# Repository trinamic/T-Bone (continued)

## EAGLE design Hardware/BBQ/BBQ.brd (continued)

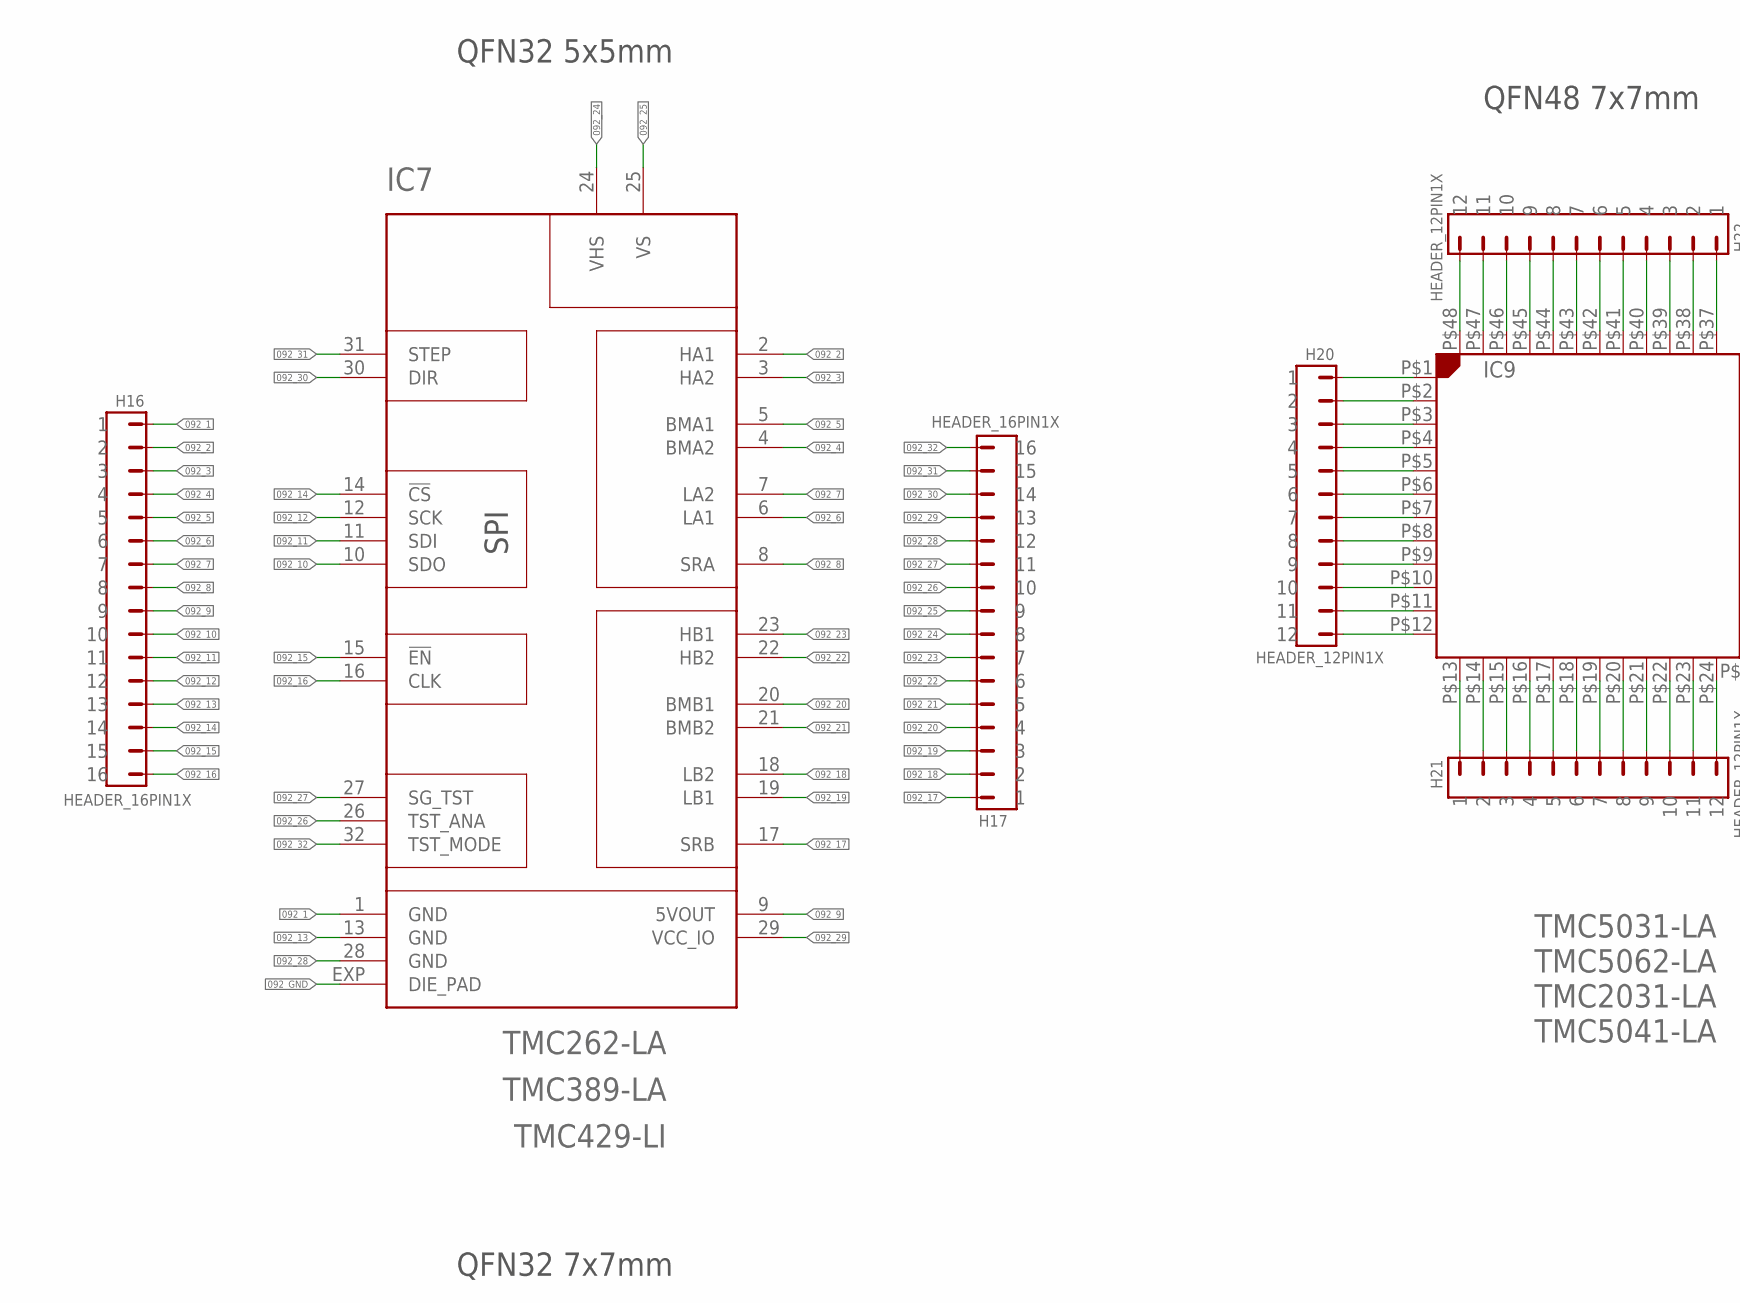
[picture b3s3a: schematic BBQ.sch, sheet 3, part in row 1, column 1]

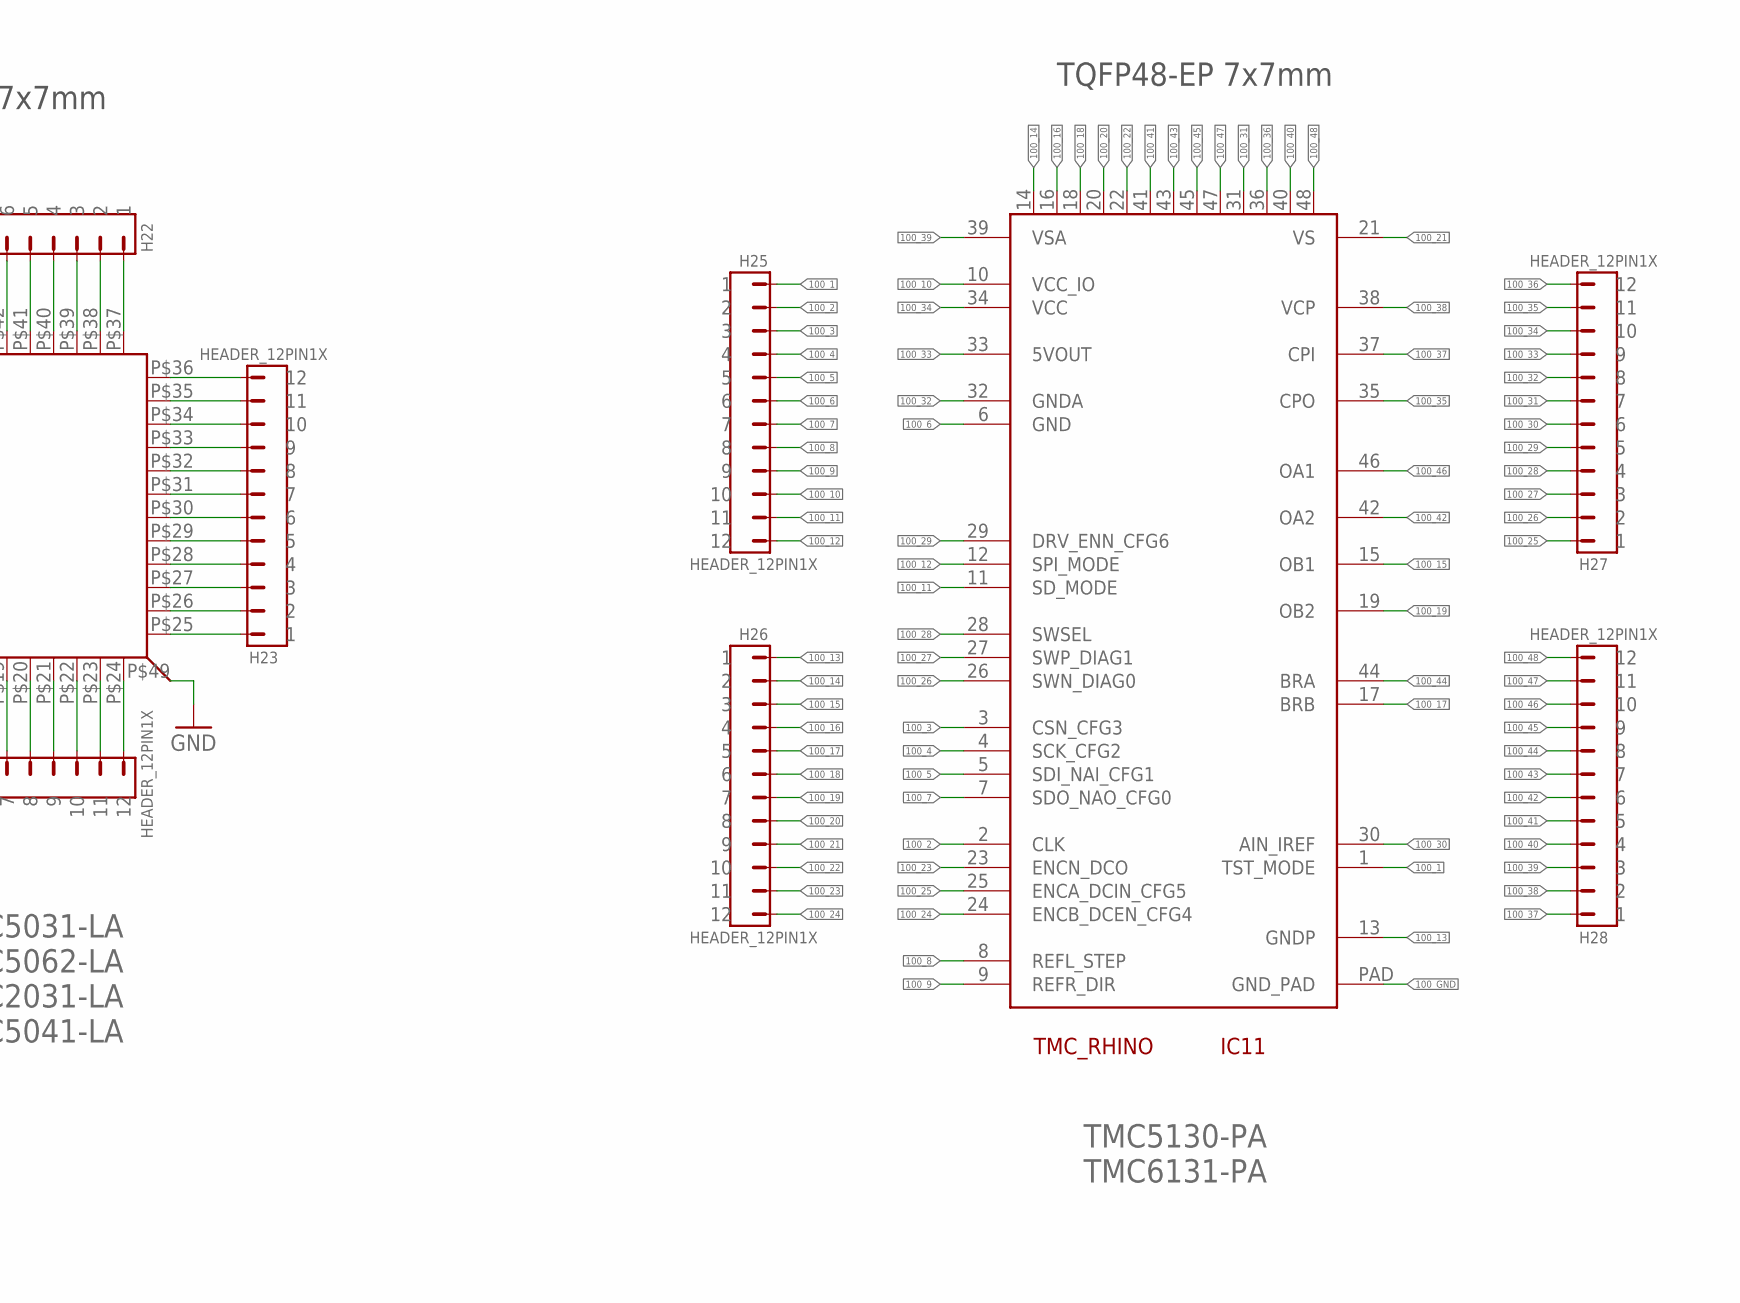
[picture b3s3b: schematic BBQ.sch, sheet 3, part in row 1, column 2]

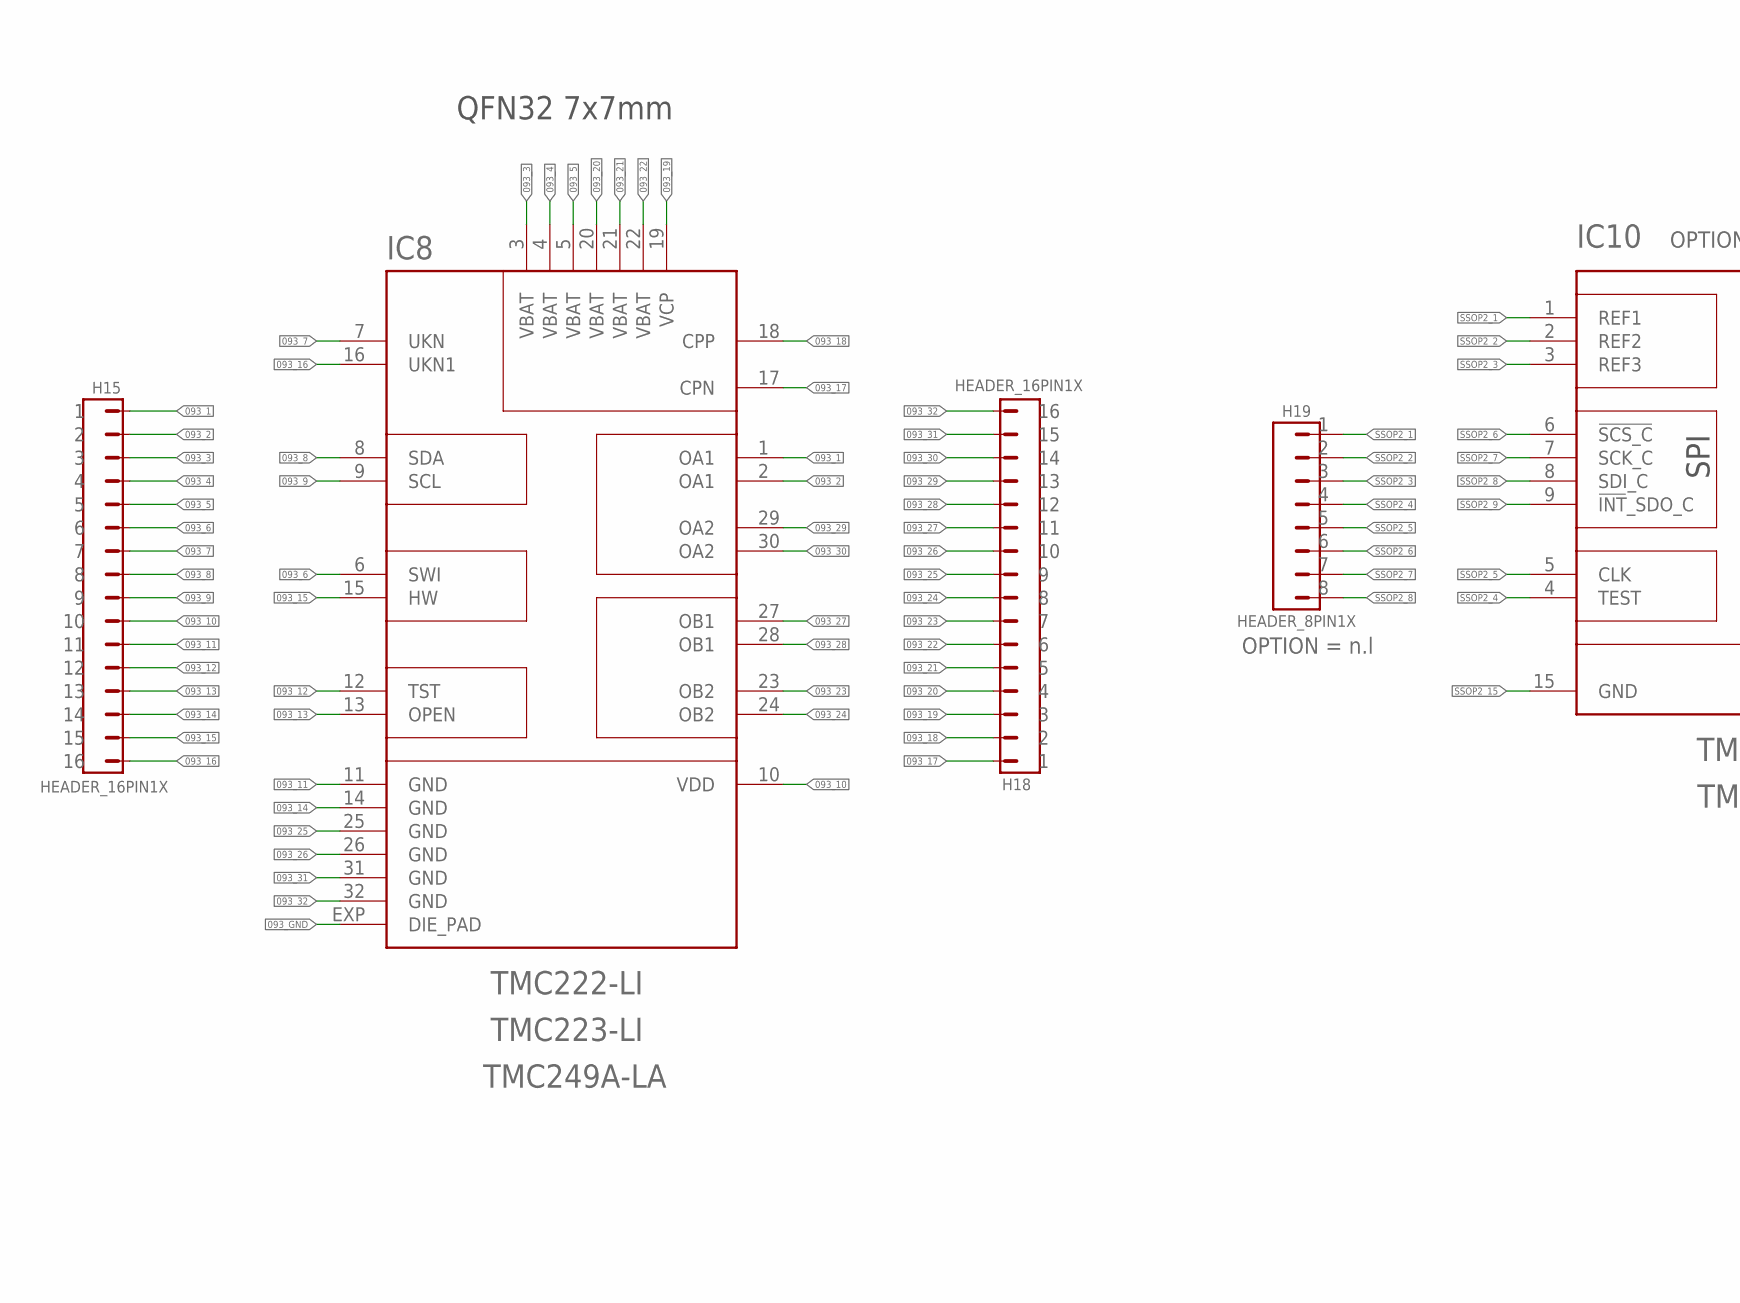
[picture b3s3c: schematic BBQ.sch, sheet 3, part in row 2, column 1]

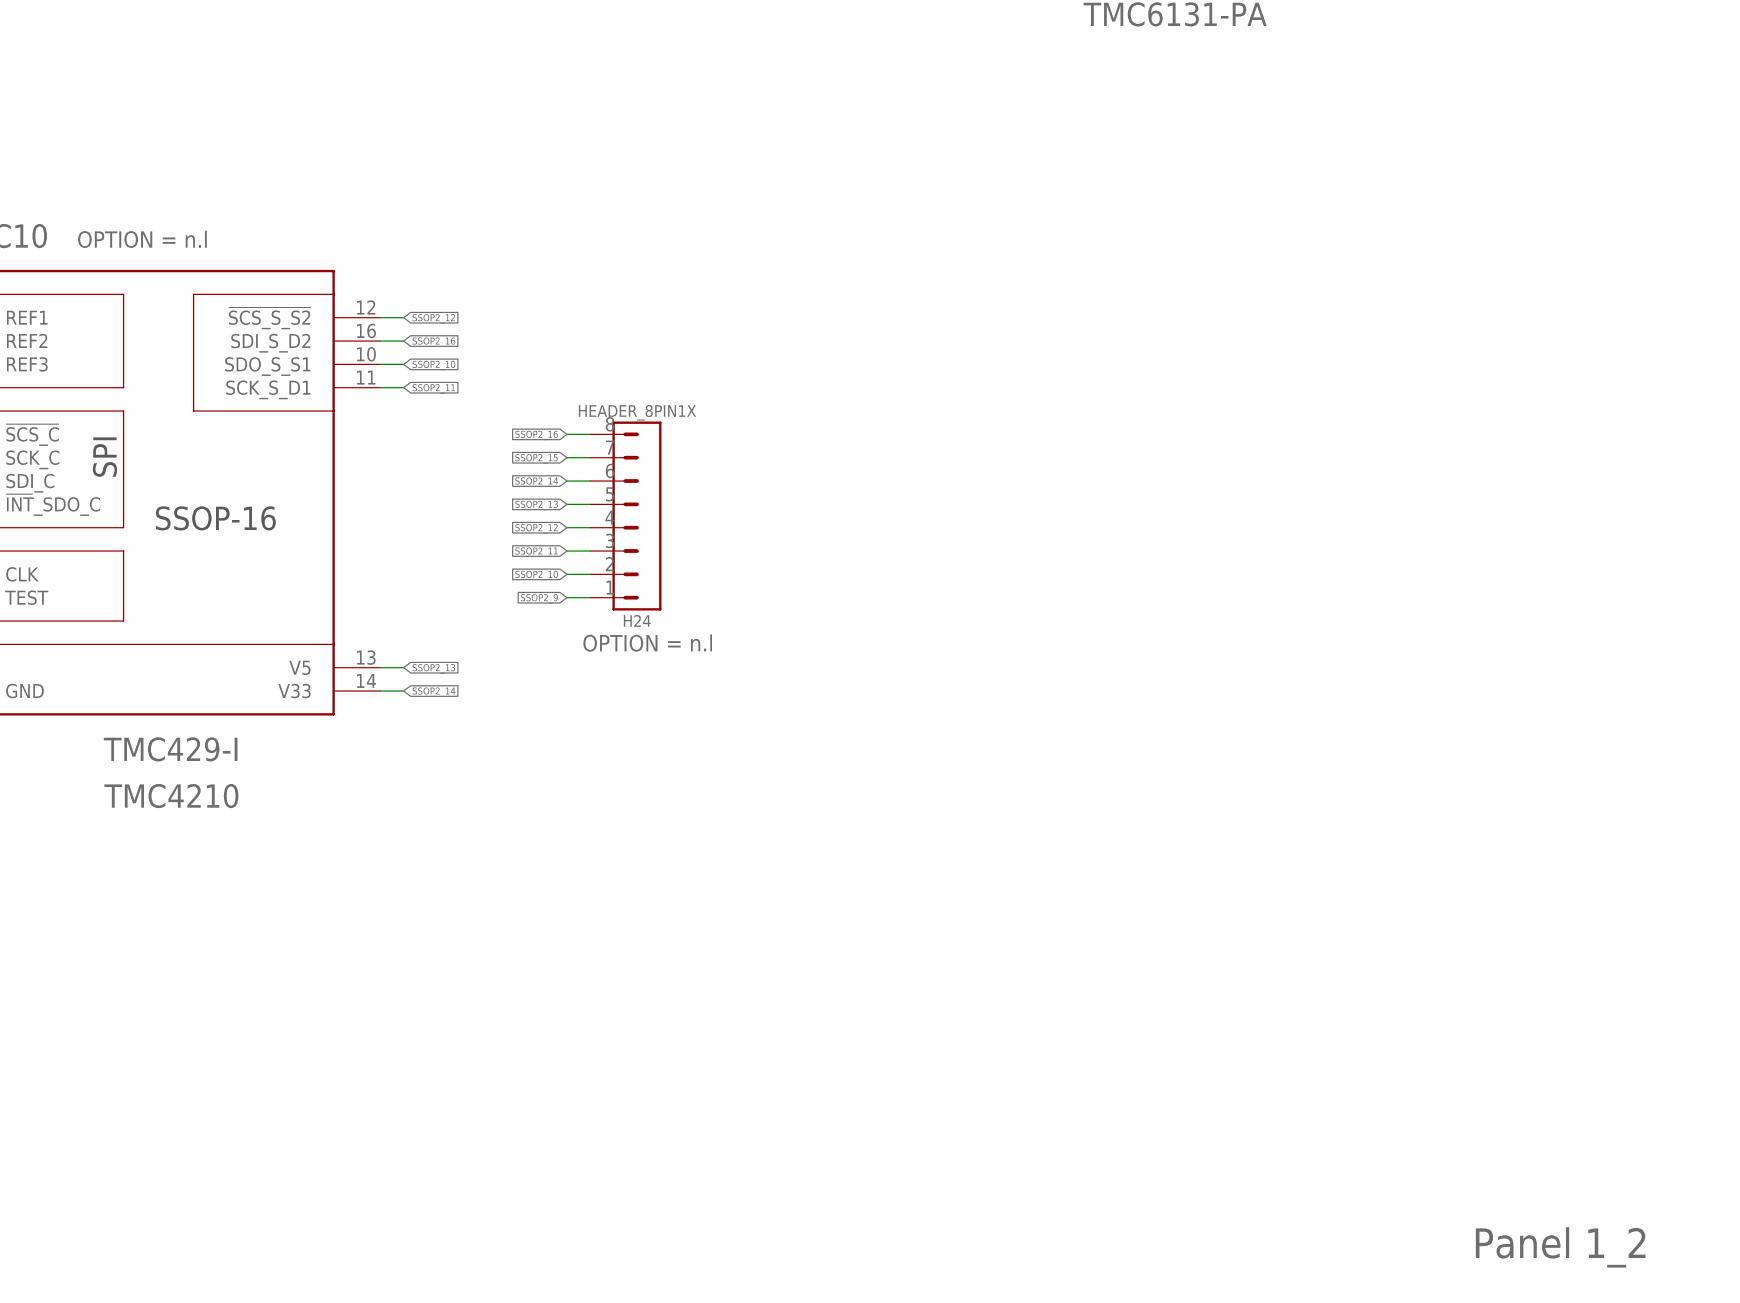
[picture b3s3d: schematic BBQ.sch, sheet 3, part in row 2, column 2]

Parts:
H15, H16, H17, H18: HEADER_16PIN1X; 16PIN_2.54_TH
H19, H24: HEADER_8PIN1X; 8PIN_2.54_TH
H20, H21, H22, H23, H25, H26, H27, H28: HEADER_12PIN1X; 12PIN_2.54_TH
IC7: TMC262-LA; QFN32_5X5
IC8: TMC222-LI; QFN32_7X7
IC9: TMC5031-LA; QFN-48_7X7
IC10: TMC429-I; SSOP16
IC11: TMC_RHINO; TQFP48-EP

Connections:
092_1: H16.1, IC7.1 (GND)
092_2: H16.2, IC7.2 (HA1)
092_3: H16.3, IC7.3 (HA2)
092_4: H16.4, IC7.4 (BMA2)
092_5: H16.5, IC7.5 (BMA1)
092_6: H16.6, IC7.6 (LA1)
092_7: H16.7, IC7.7 (LA2)
092_8: H16.8, IC7.8 (SRA)
092_9: H16.9, IC7.9 (5VOUT)
092_10: H16.10, IC7.10 (SDO)
092_11: H16.11, IC7.11 (SDI)
092_12: H16.12, IC7.12 (SCK)
092_13: H16.13, IC7.13 (GND)
092_14: H16.14, IC7.14 (!CS)
092_15: H16.15, IC7.15 (!EN)
092_16: H16.16, IC7.16 (CLK)
092_17: H17.1, IC7.17 (SRB)
092_18: H17.2, IC7.18 (LB2)
092_19: H17.3, IC7.19 (LB1)
092_20: H17.4, IC7.20 (BMB1)
092_21: H17.5, IC7.21 (BMB2)
092_22: H17.6, IC7.22 (HB2)
092_23: H17.7, IC7.23 (HB1)
092_24: H17.8, IC7.24 (VHS)
092_25: H17.9, IC7.25 (VS)
092_26: H17.10, IC7.26 (TST_ANA)
092_27: H17.11, IC7.27 (SG_TST)
092_28: H17.12, IC7.28 (GND)
092_29: H17.13, IC7.29 (VCC_IO)
092_30: H17.14, IC7.30 (DIR)
092_31: H17.15, IC7.31 (STEP)
092_32: H17.16, IC7.32 (TST_MODE)
092_GND: IC7.EXP (DIE_PAD)
093_1: H15.1, IC8.1 (OA1)
093_2: H15.2, IC8.2 (OA1)
093_3: H15.3, IC8.3 (VBAT)
093_4: H15.4, IC8.4 (VBAT)
093_5: H15.5, IC8.5 (VBAT)
093_6: H15.6, IC8.6 (SWI)
093_7: H15.7, IC8.7 (UKN)
093_8: H15.8, IC8.8 (SDA)
093_9: H15.9, IC8.9 (SCL)
093_10: H15.10, IC8.10 (VDD)
093_11: H15.11, IC8.11 (GND)
093_12: H15.12, IC8.12 (TST)
093_13: H15.13, IC8.13 (OPEN)
093_14: H15.14, IC8.14 (GND)
093_15: H15.15, IC8.15 (HW)
093_16: H15.16, IC8.16 (UKN1)
093_17: H18.1, IC8.17 (CPN)
093_18: H18.2, IC8.18 (CPP)
093_19: H18.3, IC8.19 (VCP)
093_20: H18.4, IC8.20 (VBAT)
093_21: H18.5, IC8.21 (VBAT)
093_22: H18.6, IC8.22 (VBAT)
093_23: H18.7, IC8.23 (OB2)
093_24: H18.8, IC8.24 (OB2)
093_25: H18.9, IC8.25 (GND)
093_26: H18.10, IC8.26 (GND)
093_27: H18.11, IC8.27 (OB1)
093_28: H18.12, IC8.28 (OB1)
093_29: H18.13, IC8.29 (OA2)
093_30: H18.14, IC8.30 (OA2)
093_31: H18.15, IC8.31 (GND)
093_32: H18.16, IC8.32 (GND)
093_GND: IC8.EXP (DIE_PAD)
096_GND: IC9.P$49 (EXP)
100_1: H25.1, IC11.1 (TST_MODE)
100_2: H25.2, IC11.2 (CLK)
100_3: H25.3, IC11.3 (CSN_CFG3)
100_4: H25.4, IC11.4 (SCK_CFG2)
100_5: H25.5, IC11.5 (SDI_NAI_CFG1)
100_6: H25.6, IC11.6 (GND)
100_7: H25.7, IC11.7 (SDO_NAO_CFG0)
100_8: H25.8, IC11.8 (REFL_STEP)
100_9: H25.9, IC11.9 (REFR_DIR)
100_10: H25.10, IC11.10 (VCC_IO)
100_11: H25.11, IC11.11 (SD_MODE)
100_12: H25.12, IC11.12 (SPI_MODE)
100_13: H26.1, IC11.13 (GNDP)
100_14: H26.2, IC11.14
100_15: H26.3, IC11.15 (OB1)
100_16: H26.4, IC11.16
100_17: H26.5, IC11.17 (BRB)
100_18: H26.6, IC11.18
100_19: H26.7, IC11.19 (OB2)
100_20: H26.8, IC11.20
100_21: H26.9, IC11.21 (VS)
100_22: H26.10, IC11.22
100_23: H26.11, IC11.23 (ENCN_DCO)
100_24: H26.12, IC11.24 (ENCB_DCEN_CFG4)
100_25: H27.1, IC11.25 (ENCA_DCIN_CFG5)
100_26: H27.2, IC11.26 (SWN_DIAG0)
100_27: H27.3, IC11.27 (SWP_DIAG1)
100_28: H27.4, IC11.28 (SWSEL)
100_29: H27.5, IC11.29 (DRV_ENN_CFG6)
100_30: H27.6, IC11.30 (AIN_IREF)
100_31: H27.7, IC11.31
100_32: H27.8, IC11.32 (GNDA)
100_33: H27.9, IC11.33 (5VOUT)
100_34: H27.10, IC11.34 (VCC)
100_35: H27.11, IC11.35 (CPO)
100_36: H27.12, IC11.36
100_37: H28.1, IC11.37 (CPI)
100_38: H28.2, IC11.38 (VCP)
100_39: H28.3, IC11.39 (VSA)
100_40: H28.4, IC11.40
100_41: H28.5, IC11.41
100_42: H28.6, IC11.42 (OA2)
100_43: H28.7, IC11.43
100_44: H28.8, IC11.44 (BRA)
100_45: H28.9, IC11.45
100_46: H28.10, IC11.46 (OA1)
100_47: H28.11, IC11.47
100_48: H28.12, IC11.48
100_GND: IC11.PAD (GND_PAD)
unnamed: H20.1, IC9.P$1
unnamed: H20.2, IC9.P$2
unnamed: H20.3, IC9.P$3
unnamed: H20.4, IC9.P$4
unnamed: H20.5, IC9.P$5
unnamed: H20.6, IC9.P$6
unnamed: H20.7, IC9.P$7
unnamed: H20.8, IC9.P$8
unnamed: H20.9, IC9.P$9
unnamed: H20.10, IC9.P$10
unnamed: H20.11, IC9.P$11
unnamed: H20.12, IC9.P$12
unnamed: H21.1, IC9.P$13
unnamed: H21.2, IC9.P$14
unnamed: H21.3, IC9.P$15
unnamed: H21.4, IC9.P$16
unnamed: H21.5, IC9.P$17
unnamed: H21.6, IC9.P$18
unnamed: H21.7, IC9.P$19
unnamed: H21.8, IC9.P$20
unnamed: H21.9, IC9.P$21
unnamed: H21.10, IC9.P$22
unnamed: H21.11, IC9.P$23
unnamed: H21.12, IC9.P$24
unnamed: H23.1, IC9.P$25
unnamed: H23.2, IC9.P$26
unnamed: H23.3, IC9.P$27
unnamed: H23.4, IC9.P$28
unnamed: H23.5, IC9.P$29
unnamed: H23.6, IC9.P$30
unnamed: H23.7, IC9.P$31
unnamed: H23.8, IC9.P$32
unnamed: H23.9, IC9.P$33
unnamed: H23.10, IC9.P$34
unnamed: H23.11, IC9.P$35
unnamed: H23.12, IC9.P$36
unnamed: H22.1, IC9.P$37
unnamed: H22.2, IC9.P$38
unnamed: H22.3, IC9.P$39
unnamed: H22.4, IC9.P$40
unnamed: H22.5, IC9.P$41
unnamed: H22.6, IC9.P$42
unnamed: H22.7, IC9.P$43
unnamed: H22.8, IC9.P$44
unnamed: H22.9, IC9.P$45
unnamed: H22.10, IC9.P$46
unnamed: H22.11, IC9.P$47
unnamed: H22.12, IC9.P$48
SSOP2_1: H19.1, IC10.1 (REF1)
SSOP2_2: H19.2, IC10.2 (REF2)
SSOP2_3: H19.3, IC10.3 (REF3)
SSOP2_4: H19.4, IC10.4 (TEST)
SSOP2_5: H19.5, IC10.5 (CLK)
SSOP2_6: H19.6, IC10.6 (!SCS_C)
SSOP2_7: H19.7, IC10.7 (SCK_C)
SSOP2_8: H19.8, IC10.8 (SDI_C)
SSOP2_9: H24.1, IC10.9 (!INT!_SDO_C)
SSOP2_10: H24.2, IC10.10 (SDO_S_S1)
SSOP2_11: H24.3, IC10.11 (SCK_S_D1)
SSOP2_12: H24.4, IC10.12 (!SCS_S_S2)
SSOP2_13: H24.5, IC10.13 (V5)
SSOP2_14: H24.6, IC10.14 (V33)
SSOP2_15: H24.7, IC10.15 (GND)
SSOP2_16: H24.8, IC10.16 (SDI_S_D2)

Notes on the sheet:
Panel 1_2
TMC223-LI
QFN32 7x7mm
TMC249A-LA
TMC5031-LA TMC5062-LA TMC2031-LA TMC5041-LA
QFN48 7x7mm
TMC5130-PA TMC6131-PA
TQFP48-EP 7x7mm
TMC389-LA
QFN32 5x5mm
TMC429-LI
TMC4210
SSOP-16

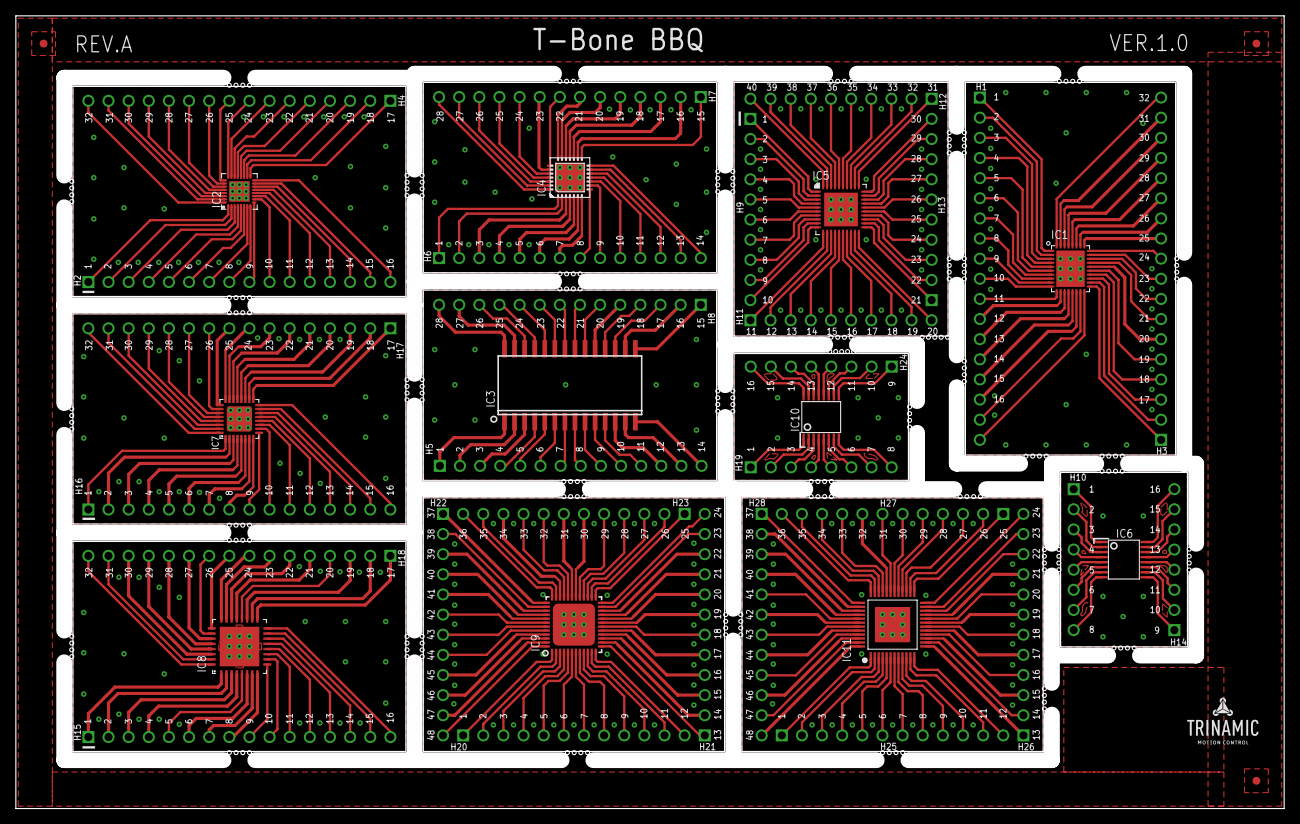
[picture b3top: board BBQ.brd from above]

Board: 2 copper layers, 160.0 x 100.0 mm, 55 parts (0 on the bottom side), 356 nets.

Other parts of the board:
U$1: TRINAMIC_LOGO
U$3, U$4, U$5, U$6, U$7, U$8, U$9, U$10, U$11, U$13, U$15, U$16: T-BONE_LOGO

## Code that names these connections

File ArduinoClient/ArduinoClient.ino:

#include <avr/interrupt.h>
#include <digitalIOPerformance.h>
#include <SPI.h>
#include <QueueArray.h>
#include <TMC26XGenerator.h>
#include <CmdMessenger.h>

#include "constants.h"
#include "types.h"

//##################
//# Debug Settings #
//##################

//#define DEBUG_MOTOR_CONTFIG
//#define DEBUG_HOMING
//#define BUG_HOMING_STATUS
//#define DEBUG_HOMING_STATUS_5041
//#define DEBUG_ENDSTOPS
//#define DEBUG_ENDSTOPS_DETAIL

//#define DEBUG_MOTION
//#define DEBUG_MOTION_SHORT
//#define DEBUG_MOTION_TRACE
//#define DEBUG_MOTION_TRACE_SHORT
//#define DEBUG_MOTION_START
//#define DEBUG_MOTION_REGISTERS
//#define DEBUG_MOTOR_QUEUE
//#define DEBUG_MOTION_STATUS
//#define DEBUG_SET_POS
//#define DEBUG_MOTOR_CONTFIG

//#define DEBUG_SPI

//#define DEBUG_STATUS
//#define DEBUG_STATUS_SHORT
//#define DEBUG_TMC5041_STATUS
//#define DEBUG_TMC4361_STATUS

#define RX_TX_BLINKY
//#define RX_TX_BLINKY_1

//how many motors do we know?
const char nr_of_coordinated_motors = 3;
const char nr_of_controlled_motors = 2;
const char nr_of_motors = nr_of_coordinated_motors + nr_of_controlled_motors;
const char homing_max_following_motors = nr_of_controlled_motors - 1;

//how much space do we have to store commands
#define COMMAND_QUEUE_LENGTH 40

//standards
#define TMC_260_CONFIG 0x8440000a //SPI-Out: block/low/high_time=8/4/4 Takte; CoverLength=autom; TMC26x
#define TMC260_SENSE_RESISTOR_IN_MO 100
#define CLOCK_FREQUENCY 16000000ul
#define DEFAULT_CURRENT_IN_MA 10
#define DEFAULT_STEPS_PER_REVOLUTION 200

#define DEFAULT_ACCELERATION 1
#define DEFAULT_BOW 1

//#define CALCULATE_OUTPUT TXLED
//the CS pins have to be defines for digitalWriteFast 
#define CS_4361_1_PIN 4
#define CS_4361_2_PIN 12
#define CS_4361_3_PIN 6
#define START_SIGNAL_PIN A3
#define CS_5041_PIN 11

#define INT_5041_PIN 8
#define INT_4361_1_PIN 3
#define INT_4361_2_PIN 2
#define INT_4361_3_PIN 7

#define PWM1_PIN 9
#define PWM2_PIN 10

#define TEMP1_PIN A0
#define TEMP2_PIN A1
#define TEMP3_PIN A2

#define FB1_PIN A4
#define FB2_PIN A5

TMC4361_info motors[nr_of_coordinated_motors] = {
  {
    INT_4361_1_PIN,0, motor_1_target_reached, 
    TMC26XGenerator(DEFAULT_CURRENT_IN_MA,TMC260_SENSE_RESISTOR_IN_MO),
    DEFAULT_STEPS_PER_REVOLUTION                    }
  ,
  {
    INT_4361_2_PIN,1, motor_2_target_reached, 
    TMC26XGenerator(DEFAULT_CURRENT_IN_MA,TMC260_SENSE_RESISTOR_IN_MO), 
    DEFAULT_STEPS_PER_REVOLUTION                     }
  ,
  {
    INT_4361_3_PIN,4, motor_3_target_reached, 
    TMC26XGenerator(DEFAULT_CURRENT_IN_MA,TMC260_SENSE_RESISTOR_IN_MO), 
    DEFAULT_STEPS_PER_REVOLUTION                     }
};


#define DEFAULT_COMMAND_BUFFER_DEPTH (nr_of_motors)

//how many otors can be theoretically geared together
#define MAX_FOLLOWING_MOTORS (nr_of_motors-1)


motion_state current_motion_state = no_motion;
//this bitfiled store which motors are invesed - _BV(1) means the motor is inversed)
unsigned char inverted_motors;



volatile boolean next_move_prepared = false;
volatile boolean move_executing = false;
volatile unsigned int motor_status;
volatile unsigned char target_motor_status;
volatile unsigned char next_target_motor_status;
volatile unsigned char differential_encoder_motors;
char direction[nr_of_coordinated_motors];
char next_direction[nr_of_coordinated_motors];
unsigned char min_buffer_depth = DEFAULT_COMMAND_BUFFER_DEPTH;


//config

QueueArray<movement> moveQueue = QueueArray<movement>(COMMAND_QUEUE_LENGTH);


//somebody must deal with our commands
CmdMessenger messenger = CmdMessenger(Serial1);

void setup() {
  //pwm is done in the bbb
  pinModeFast(PWM1_PIN,INPUT);
  digitalWriteFast(PWM1_PIN,LOW);
  pinModeFast(PWM2_PIN,INPUT);
  digitalWriteFast(PWM2_PIN,LOW);

  //switch the analog pins as innput to hand them over to the BBB
  pinModeFast(TEMP1_PIN,INPUT);
  digitalWriteFast(TEMP1_PIN,LOW);
  pinModeFast(TEMP2_PIN,INPUT);
  digitalWriteFast(TEMP2_PIN,LOW);
  pinModeFast(TEMP3_PIN,INPUT);
  digitalWriteFast(TEMP3_PIN,LOW);
  pinModeFast(FB1_PIN,INPUT);
  digitalWriteFast(FB1_PIN,LOW);
  pinModeFast(FB1_PIN,INPUT);
  digitalWriteFast(FB1_PIN,LOW);

  //initialize SPI
  SPI.begin();
  SPI.setClockDivider(SPI_CLOCK_DIV2);

  // Use HWBE as Output
  DDRE |= _BV(2);                    // set HWBE pin as output (Fuse HWBE disabled, point to check..)

  // Analog reference AREF
  analogReference(EXTERNAL);

  //set the TMC4361 ipns correctly
  prepareTMC4361();
  //set the TMMC5041 pins correctly
  prepareTMC5041();

  //at least we should try deactivate the motion drivers
  resetTMC4361(true, true);


  //initialize the serial port for commands
  Serial1.begin(38400);
  Serial.begin(115200);

  //set the serial as debug output 
  moveQueue.setStream(Serial);

#ifdef CALCULATE_OUTPUT
  pinModeFast(CALCULATE_OUTPUT, OUTPUT);
  digitalWriteFast(CALCULATE_OUTPUT,LOW);
#endif

  // Adds newline to every command
  messenger.printLfCr();   

  // Attach my application's user-defined callback methods
  attachCommandCallbacks();

  //finally signal that we are ready
  watchDogStart();

}

unsigned long last_millis=0;

void loop() {
  //move if neccessary
  checkMotion();
  // Process incoming serial data, and perform callbacks
  messenger.feedinSerialData();

  if (millis()-last_millis>1000) {
#ifdef RX_TX_BLINKY
    TXLED1;
#endif
    watchDogPing();
    last_millis=millis();
#ifdef RX_TX_BLINKY
    TXLED0;
#endif
  }
}

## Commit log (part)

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2014-03-11 and suddenly it works??
2014-03-11 it seems that we have to read the registers and do it asynchornously ...
2014-03-11 a lot of complication with move & follow … for 5041 …
2014-03-11 let's see if it works …
2014-03-11 go faster??
    btw why is x so slow …
2014-03-11 this is the extruder config
2014-03-11 and this should parse it …
2014-03-12 we do the configuration a bit easier …
2014-03-12 those gcodes are easy to implement
    by ignoring and warning …
2014-03-12 it is z axis …
2014-03-12 this absoulte/relative posion things is somehtig we could do …
2014-03-12 this should enable the set position ? …
2014-03-12 slight adaptions of the extruder
2014-03-12 hmm there was some subtle difference …
2014-03-12 this should add the extruder movements …
2014-03-12 we should really reconsider calulating the speeds …
2014-03-12 typo
2014-03-12 ok, this moves the extruder …
2014-03-12 implementing the pid controller was easy
2014-03-12 - ok this is a beginning for the temperature control config
2014-03-12 in theory is the 3rd pwm also usable
2014-03-13 adding a license
2014-03-13 setup.py thankfully stolen from octoprint
2014-03-13 moving arduino tests to own directory
2014-03-13 this belongs here …
2014-03-13 was boring anyway
2014-03-13 this belongs here too
2014-03-13 we need numpy
2014-03-13 the installer
2014-03-13 now it is a script
2014-03-13 this is just a test
2014-03-13 huh, still there?
2014-03-13 and all this is src
2014-03-13 we need this
2014-03-13 we got tests
2014-03-13 more test requirements
2014-03-13 it is PyHamcrest
2014-03-13 hmm test does not like '-'
2014-03-13 this better belongs here
2014-03-13 oops
2014-03-13 at least the mendel thermistors
2014-03-14 we want to debug homing and endstops …
2014-03-14 homing only - sketch too big - let's slim down
2014-03-14 ok, metro is perhaps a bit over the top …
2014-03-14 ok the config is now really fix!
2014-03-14 and the printer config for trinamic
2014-03-14 this should be - more or less the trinamic printer
    let's see …
2014-03-16 ok the printer config comes after all axis
2014-03-16 do we get a raw temperature reading?
2014-03-16 lots of little corrections
2014-03-16 now correctly starting the heater
2014-03-16 calculating a proper temperature reading is not so hard …
2014-03-16 looks a bit complicated - but should give us some current reading …
2014-03-16 hmm we want to shut down the port anyway!
2014-03-16 hmm switching btw GPIO & PWM does not work??
2014-03-17 hmm there was a lot of text in the return codes
    let's reduce the code size by giving back numbers only. Sad but
    neccessary
2014-03-17 why don't we just give an additional parameter tohome to the right?
2014-03-17 this should be the right (direction) homing??
2014-03-17 we reduce the number of times we switch on the heated bed
2014-03-17 ok lets' test the homing to the right.
2014-03-17 hmm shouldn't we set the postion of the left virutal endstop to 0??
2014-03-17 hmm there seems to be a problem with the heated bed??
2014-03-17 ok, this homes x
    but y is broken??
2014-03-17 debugging the 5041 alone
    because the sketch got too big
2014-03-17 we start again with the heater and do not readout the current every time
2014-03-17 ok, this seems to crrect the temperature reading
2014-03-17 this could be the heating
2014-03-17 hmm we shoudl give back the real temperaturees, not the input value
2014-03-19 this homes a bit better
2014-03-19 ok - the endstops are write onlay in the 5041
2014-03-19 dammit - the endstop config was inevrsed
2014-03-19 this is the adapted dev printer config
2014-03-19 the extruder heater and the heated bed are basically the same
2014-03-19 what is wrong with the second PWM channel?
2014-03-20 morning cosmetics
2014-03-20 better cleanup?
2014-03-20 really setting positions - in theory
2014-03-20 little stuff to make it run again
2014-03-20 okaye, the parameter is s…
2014-03-21 separate print and move
2014-03-21 ok we can set the extruder temperature
2014-03-21 in theory this is how we could move the axis …
2014-03-21 this should move the printer - but it does not
2014-03-21 cosmetics
2014-03-21 don't we have to use the previous movement as well?
2014-03-21 hmm why does the motion not finish
2014-03-21 hmm moving only left is useless
2014-03-23 default speed is 10mm/s
    and singular movement are always stops
2014-03-23 if we finish a motion ist ends - so complete x & y stop
2014-03-23 it seems like we can increase the SPI speed …
2014-03-23 optimizing the PID Controller …
2014-03-23 dammit - wrong name
2014-03-24 it sets the temperature
2014-03-24 you should write to the correct motors …
2014-03-24 nulling a bit more the last target
2014-03-24 this prepare_shaddow_registers was rubbish anyway
2014-03-24 upping the trinamic printer config
2014-03-24 hmm this was the config
2014-03-24 ui we forgot to write the interrupt registers
2014-03-24 now configurable pwm frequency for the fan
2014-03-24 epcos 100k thermistor reprapteile.de
    New table, makes sense?
2014-03-24 better?!
2014-03-25 it did a complete move
2014-03-25 this should set all those nifty set positions a bit better
2014-03-25 it is favourable to preserve the set position
2014-03-25 ok it seems as we can safely cacluate the extruder speed …
2014-03-25 ok it seems that we now scale the extruder correctly
2014-03-25 hmm on debug it is much more quiet
2014-03-25 better error logging
2014-03-25 more elaborate debugging
2014-03-25 Duty cycle fan and hotend
2014-03-25 it seems that slower serial brings less problems
2014-03-25 we home onlay once
    this is rubbish
2014-03-25 we also want to move if it is a manual move
2014-03-25 wrong config changed for extruder current
2014-03-26 let's speed up things a bit
2014-03-26 ok, that is how it is run …
2014-03-26 a bit more documentation
2014-03-26 hmm the homing prevention does not work reliably
2014-03-26 better?
2014-03-26 not needed
2014-03-26 more buffer more good
2014-03-26 a bit more colours with leds??
2014-03-26 a led even in the move??
2014-03-26 this is what we measured
2014-03-26 a new set of config for printing
2014-03-26 hmm this should mke it reach temperature
2014-03-26 wrong error message
2014-03-26 slowly homing in …
2014-03-27 hmm we have to introduce our own new pins file to avoid cyclic dependencies
2014-03-27 ok, but this gives problems with extrusion …
2014-03-27 he said that there should not be too much acceleration & bow
2014-03-27 slight todoes and cosmetics
2014-03-27 hmm this was wrong
2014-03-31 starting the stallguard test
    … with something we already have …
2014-03-31 we need a notion of speed
2014-03-31 so far more standard code …
2014-03-31 organizing the reset code
2014-03-31 hej this is a test
2014-03-31 enough preparation
2014-03-31 it seems that it is kinda working
2014-03-31 let's wait until we are 'fast' enough
2014-04-01 slight cosmetics
2014-04-01 going back and forth reduces calibration width
2014-04-01 in theory we can go there to crash into the mechanic …
2014-04-01 this seems to work
    homing with SG!
2014-04-01 fiddling
2014-04-04 this is the current scaling config
2014-04-04 better current config
2014-04-14 this unkown command reply is more usable
2014-04-14 hmm we should be able to set multiple motor axis to a value …
2014-04-14 we have a xy unit ..
2014-04-15 at least crashing if acceleration is too high
    much better than wrap around
2014-04-15 at least we can show the config …
2014-04-15 it seems that we can write the config
2014-04-15 ok, wait and info is definitively different …
2014-04-15 wait while homing …
2014-04-15 minor corrections
2014-04-15 also pinging for the z-axis?!
2014-04-15 searching for the perfect thermistor
2014-04-15 dammit forgotten
2014-04-15 loggabit
2014-04-16 huh, forgot the import …
2014-04-16 thermistor mini optimiztaion
2014-04-16 optimizing the PID
2014-04-16 remove redundant paranthesis
2014-04-17 improve start routine
    nad some better debugging …
2014-04-17 screwing the printer config
2014-04-17 still some too high acceleration problems …
2014-04-17 go faster
2014-04-17 beauty
2014-04-17 nasty, the start config was not written for right homing
2014-04-17 motion debugging
2014-04-17 no debug
2014-04-17 Some things I wonder about/changed
    Sense reesistors in Arduino Software wrong (thing not a problem since
    configured in BB)
    Motion.ino seems to be sth. wrong?!
2014-04-28 disabling the X-server
2014-04-28 verify by commenting
2014-04-28 this should reduce most critical scale problems …
2014-04-28 this seems like a nice way to prevent overshoot errors
    ...
2014-04-28 huh, don't we need to buffer the next target as well
2014-04-28 and testing at full speed
2014-04-28 those simple tricks can really wreck your movement
2014-04-28 it really annoyed me that you cannot just home all axis
2014-04-29 improving the speed calculations?
2014-04-29 hmm the old code made more sense with the tests
2014-04-30 it seems that stopping at e movements is not that hard
2014-04-30 faster spi?
2014-04-30 better printer config?
2014-04-30 changing acceleration
2014-05-05 LED PIN assignment wrong
    correction of LED PINs
2014-05-27 schematic and board of last T-Bone version
    Added "CC-BY SA" text
    Some changes still have to be made..
    (Commented on interactive-matter projects site)
2014-05-27 Breakout Boards, Holder Prusa I3, Silkscreen, BOM
    Added some other files from the project
2014-07-08 oh we forgot the starting from 0 speed …
2014-07-09 it seems that some odd things can happen …
2014-07-09 we had to recalculate the calculations …
2014-07-10 ok setting the position also has to change the current value …
2014-07-10 ok, the length calculations were the problems of the movement …
2014-07-10 let's try the ehated bed again …
2014-07-10 log file massage
2014-07-11 ok the heat may have come from the heated bed - but this is long gone …
2014-07-11 this enables the heated bed
2014-07-11 this heater version worked far better
2014-07-11 for security reasons we should also correlate the speed
2014-07-11 we should not convert the steps to ints - to retain precision
    for relative calculations
2014-07-14 naming is everything …
2014-07-14 to consider stopping we must consider more options
2014-07-14 tests have shown tahat the formulas were wrong
2014-07-14 if the next move is no move we have to cnsider the stop …
    … in speed calculations
2014-07-14 we can assume taht accleration and deceleration take the same time
2014-07-15 ok slight corrdctions lead to the correct acceleration
2014-07-16 some preparations for adding different heater methods
2014-07-16 and this could be the on/off heater
2014-07-16 more structure makes it easier to add more thermistor methods
2014-07-16 adding the replicape thermistors
2014-07-16 this is a better cleanup
2014-07-16 what a silly error
2014-07-16 the gcode interpretation for the heated bed is a bit different
2014-07-30 Testcode for stresstest
    Test machine?
2014-08-07 we want to test the buffer adding
    and reduced the buffer size - which seems to solve the problem …
2014-08-07 we switch back to normal blinky
2014-09-16 this should give the encoder position
2014-09-17 dammit, you should test the code
2014-09-18 we should configure the encoder, shouldn't we?
2014-09-18 d'oh
2014-11-18 Changed Sense Resistors, TMC2660 = 100mOhm, added SQRT_2 to TMC26XGenerator.cpp
2014-11-18 Just deleted a line at the beginning
2014-12-02 Changed folder structure
    Added Hardware schematics and board design for T-Bone
    Added Hardware schematics and board design for BBQ breakout board
    Added Hardware schematics for Programming board for T-Bone
2014-12-03 Added Software Documentation Added T-Bone UART command documentation with example protocol
2014-12-03 Renamed digitalIOPerformance lib Added library installation link
2014-12-03 Added more files for TMC2100-BOB
    Added LICENSE file which is effective for the software
2014-12-03 Updated readme file
2014-12-03 Restructured folder structure
2014-12-04 Changed software documentation design
2014-12-10 Updated TMC26XGenerator.cpp
2014-12-21 Update setup.py
    Change the path for the README.md-File.
2015-02-05 Major software update
